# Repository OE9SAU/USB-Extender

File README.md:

# USB Extender

CH315G is a USB extension control chip, used for USB signal real time transmit and extend transfer distance.
The USB signal extension circuit in the CH315G, support category 5 or category 5 unshielded twisted-pair cables, 
and the transfer distance is no less than 75m of 12Mbps full-speed USB signal, the transfer distance is no less than 300m of 1.5Mbps.

v2: 
* wrong footprint for USBLC6-2 (SOT666->SOT23-6)
* add R1.1 LED choice for RJ45 plug
* wrong marking SLAVE<->MASTER, new: MASTER<->SLAVE

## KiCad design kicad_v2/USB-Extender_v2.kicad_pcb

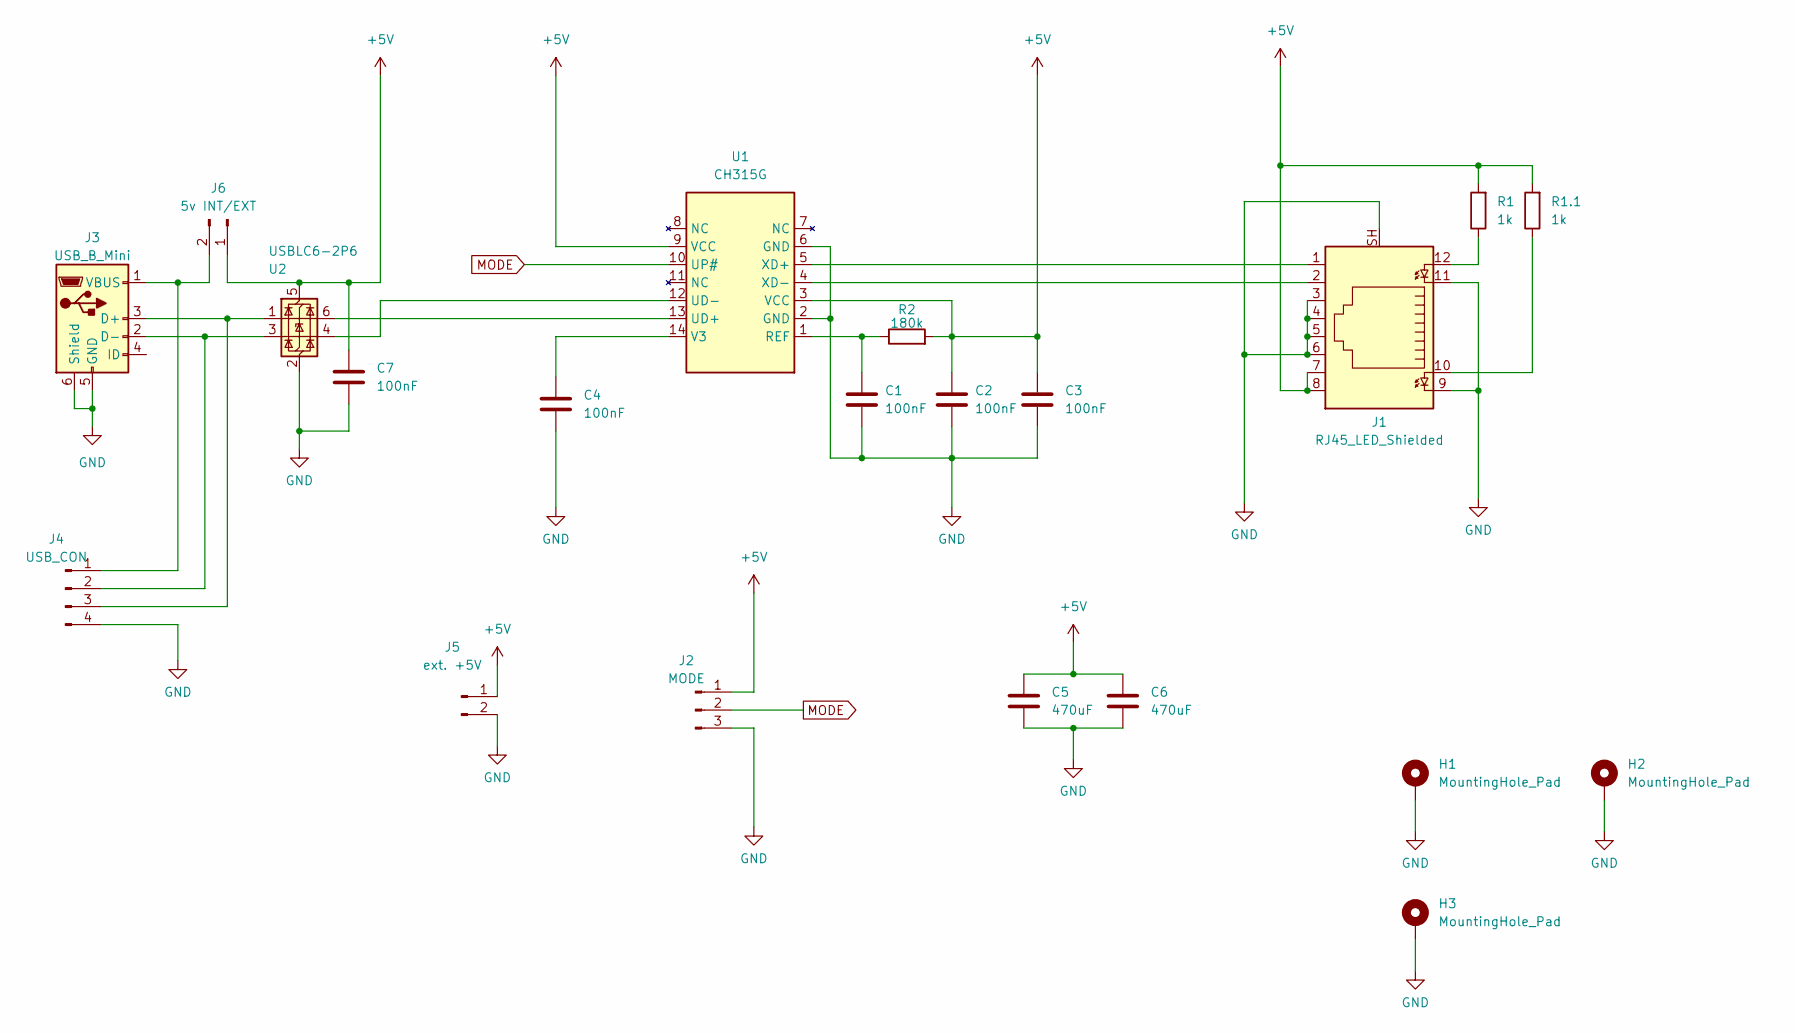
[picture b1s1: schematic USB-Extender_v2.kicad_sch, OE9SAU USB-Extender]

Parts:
C1, C2, C3, C4, C7: 100nF; C_0805_2012Metric_Pad1.18x1.45mm_HandSolder
C5, C6: 470uF; CP_Elec_6.3x7.7
H1, H2, H3: MountingHole_Pad; MountingHole_2.2mm_M2_ISO7380_Pad
J1: RJ45_LED_Shielded; RJ45_Amphenol_RJHSE538X
J2: MODE; PinHeader_1x03_P2.54mm_Vertical
J3: USB_B_Mini; USB_Mini-B_Wuerth_65100516121_Horizontal
J4: USB_CON; PinHeader_1x04_P2.54mm_Horizontal
J5: ext. +5V; PinHeader_1x02_P2.54mm_Vertical
J6: 5v INT/EXT; PinHeader_1x02_P2.54mm_Vertical
R1, R1.1: 1k; R_0805_2012Metric_Pad1.20x1.40mm_HandSolder
R2: 180k; R_0805_2012Metric_Pad1.20x1.40mm_HandSolder
U1: CH315G; SOIC-14_3.9x8.7mm_P1.27mm
U2: USBLC6-2P6; SOT-23-6_Handsoldering

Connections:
+5V: C2.1, C3.1, C5.1, C6.1, C7.1, J1.7, J1.8, J2.1, J5.1, J6.1, R1.2, R1.1.2, R2.2, U1.3 (VCC), U1.9 (VCC), U2.5 (VBUS)
GND: C1.2, C2.2, C3.2, C4.2, C5.2, C6.2, C7.2, H1.1, H2.1, H3.1, J1.3, J1.4, J1.5, J1.6, J1.9, J1.11, J1.SH, J2.3, J3.5 (GND), J3.6 (Shield), J4.4, J5.2, U1.2 (GND), U1.6 (GND), U2.2 (GND)
MODE: J2.2, U1.10 (UP#)
unnamed: J1.10, R1.1.1
unnamed: J1.12, R1.1
unnamed: J3.3 (D+), J4.3, U2.1 (I/O1)
unnamed: J3.2 (D-), J4.2, U2.3 (I/O2)
unnamed: J3.1 (VBUS), J4.1, J6.2
unnamed: C1.1, R2.1, U1.1 (REF)
unnamed: U1.13 (UD+), U2.6 (I/O1)
unnamed: U1.12 (UD-), U2.4 (I/O2)
unnamed: C4.1, U1.14 (V3)
unnamed: J1.1, U1.5 (XD+)
unnamed: J1.2, U1.4 (XD-)

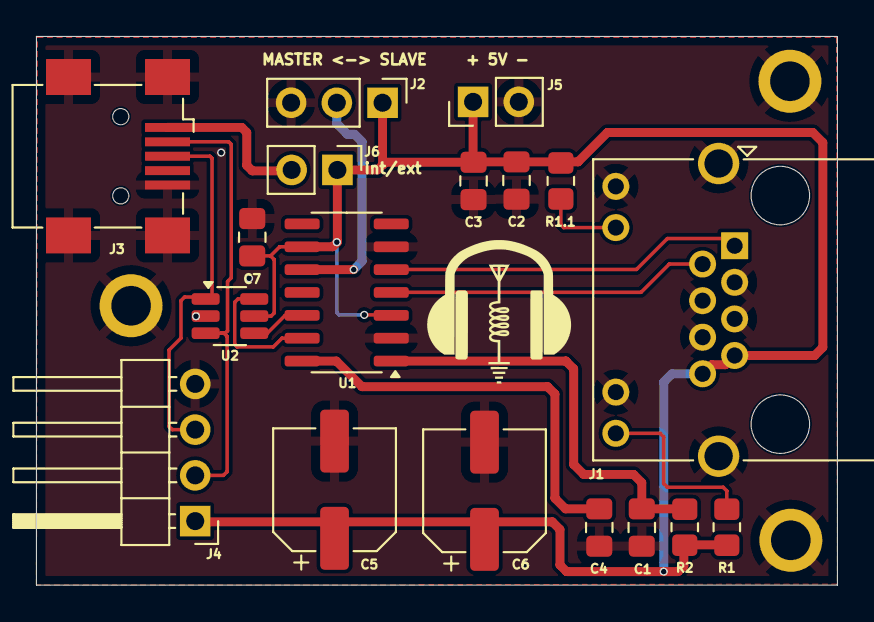
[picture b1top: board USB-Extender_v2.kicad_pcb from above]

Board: 2 copper layers, 44.5 x 30.5 mm, 23 parts (1 on the bottom side), 14 nets.

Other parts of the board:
g1, g2: LOGO

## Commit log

2024-10-09 Update V1
2024-10-10 Upreadme
2024-10-10 Update vias
2024-10-10 Update Number
2024-10-29 Cleanup
2024-11-01 PCB v2
    Footprint change
2024-11-01 Update v2
2025-02-12 Uodate
